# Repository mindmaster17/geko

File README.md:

# geko
A custom-designed split mechanical keyboard built from the ground up using the ESP32 microcontroller

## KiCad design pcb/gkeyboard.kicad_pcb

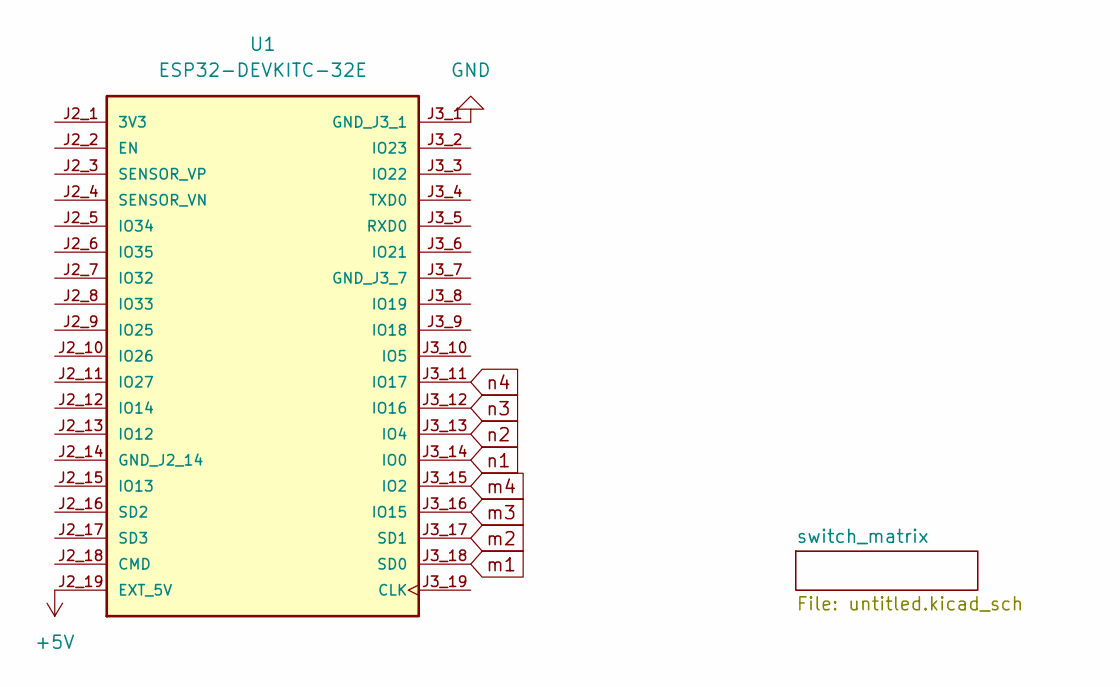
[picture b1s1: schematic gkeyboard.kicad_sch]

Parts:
U1: ESP32-DEVKITC-32E; MODULE_ESP32-DEVKITC-32E; PARTREV 1.4

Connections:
+5V: U1.J2_19 (EXT_5V)
GND: U1.J3_1 (GND_J3_1)
m1: U1.J3_11 (IO17), U1.J3_12 (IO16), U1.J3_13 (IO4), U1.J3_14 (IO0), U1.J3_15 (IO2), U1.J3_16 (IO15), U1.J3_17 (SD1), U1.J3_18 (SD0); also elsewhere on the board

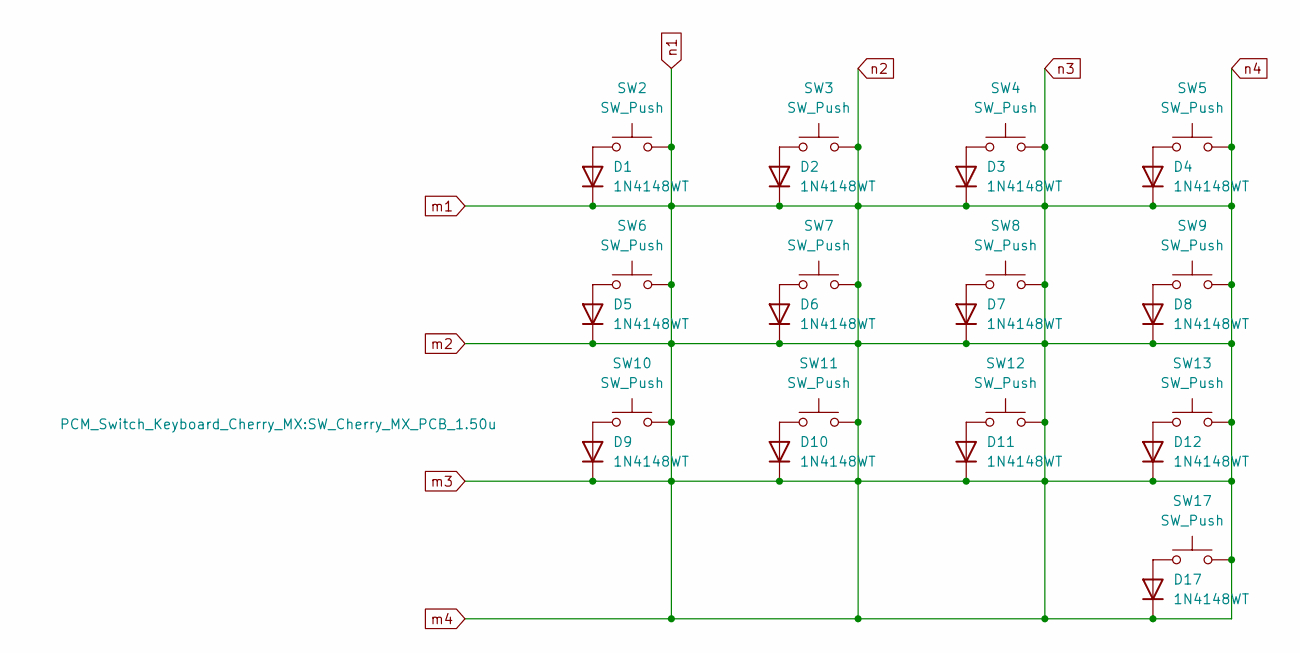
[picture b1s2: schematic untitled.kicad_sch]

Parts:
D1, D2, D3, D4, D5, D6, D7, D8, D9, D10, D11, D12, D17: 1N4148WT; D_1206_3216Metric_Pad1.42x1.75mm_HandSolder
SW2, SW3, SW4, SW5, SW6, SW7, SW8, SW9, SW11, SW12, SW13: SW_Push; SW_Cherry_MX_PCB_1.00u
SW10: SW_Push; SW_Cherry_MX_PCB_1.50u
SW17: SW_Push; SW_Cherry_MX_PCB_2.00u

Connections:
unnamed: D1.2 (A), SW2.1
unnamed: D2.2 (A), SW3.1
unnamed: D3.2 (A), SW4.1
unnamed: D4.2 (A), SW5.1
unnamed: D5.2 (A), SW6.1
unnamed: D6.2 (A), SW7.1
unnamed: D7.2 (A), SW8.1
unnamed: D8.2 (A), SW9.1
unnamed: D9.2 (A), SW10.1
unnamed: D10.2 (A), SW11.1
unnamed: D11.2 (A), SW12.1
unnamed: D12.2 (A), SW13.1
unnamed: D17.2 (A), SW17.1
m1: D1.1 (K), D2.1 (K), D3.1 (K), D4.1 (K), D5.1 (K), D6.1 (K), D7.1 (K), D8.1 (K), D9.1 (K), D10.1 (K), D11.1 (K), D12.1 (K), D17.1 (K), SW2.2, SW3.2, SW4.2, SW5.2, SW6.2, SW7.2, SW8.2, SW9.2, SW10.2, SW11.2, SW12.2, SW13.2, SW17.2; also elsewhere on the board

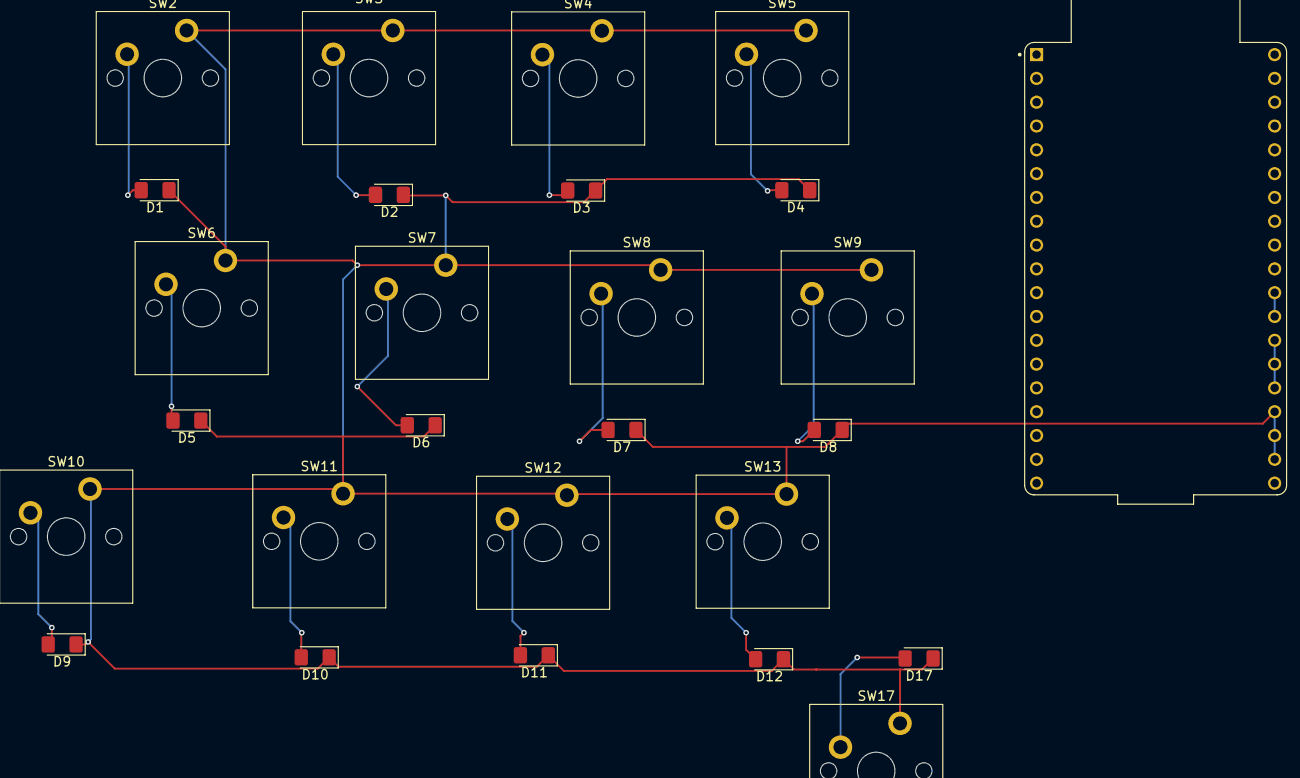
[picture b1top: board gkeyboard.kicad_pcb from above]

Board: 2 copper layers, 27 parts (0 on the bottom side), 14 nets.

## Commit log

2026-01-09 Add .gitignore for KiCad project files
2026-01-10 Add image to README for Geko keyboard
